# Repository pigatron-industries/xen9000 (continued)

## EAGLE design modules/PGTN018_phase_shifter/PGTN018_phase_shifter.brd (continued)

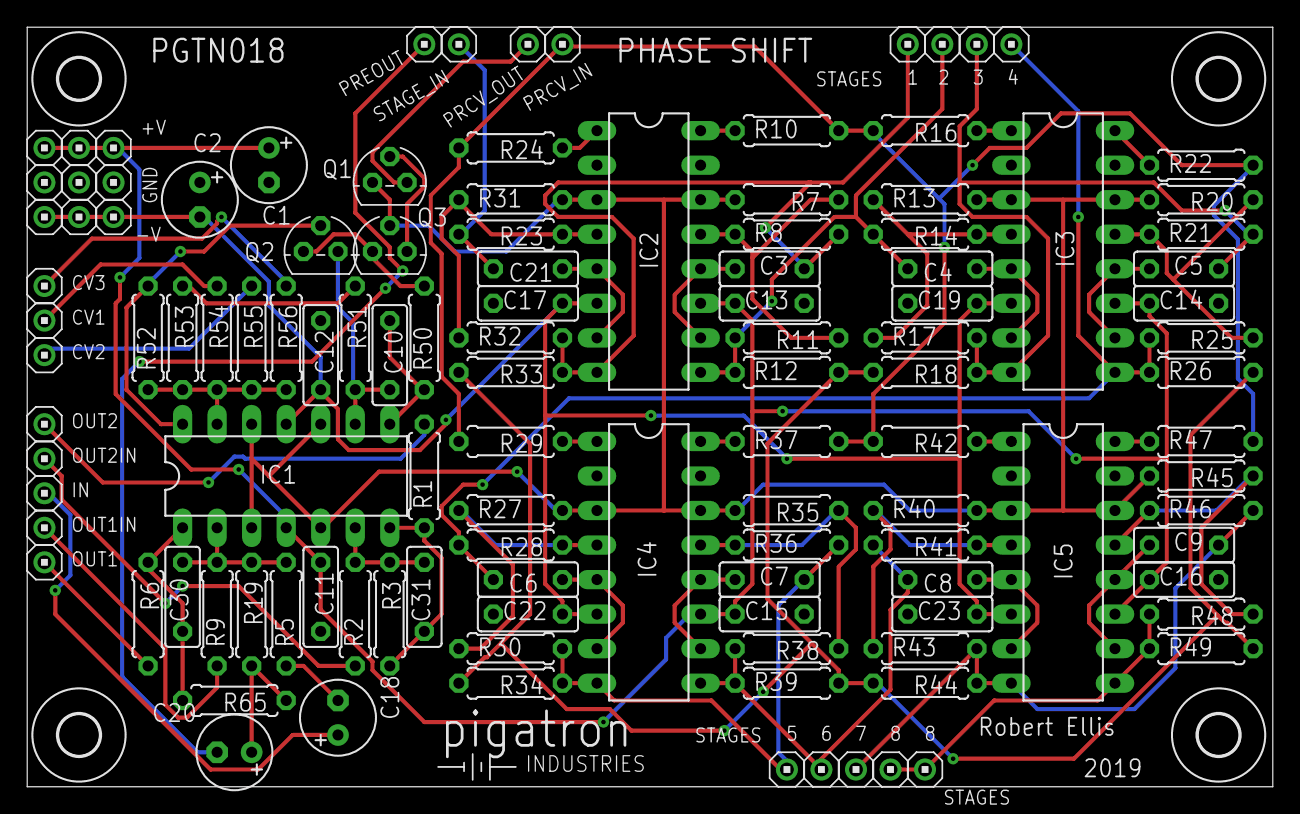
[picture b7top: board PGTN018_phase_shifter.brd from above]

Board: 2 copper layers, 91.6 x 55.9 mm, 123 parts (0 on the bottom side), 62 nets.

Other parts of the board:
U$1, U$2, U$3, U$4: STANDOFF/3.0
U$5: PIGATRON-LOGO

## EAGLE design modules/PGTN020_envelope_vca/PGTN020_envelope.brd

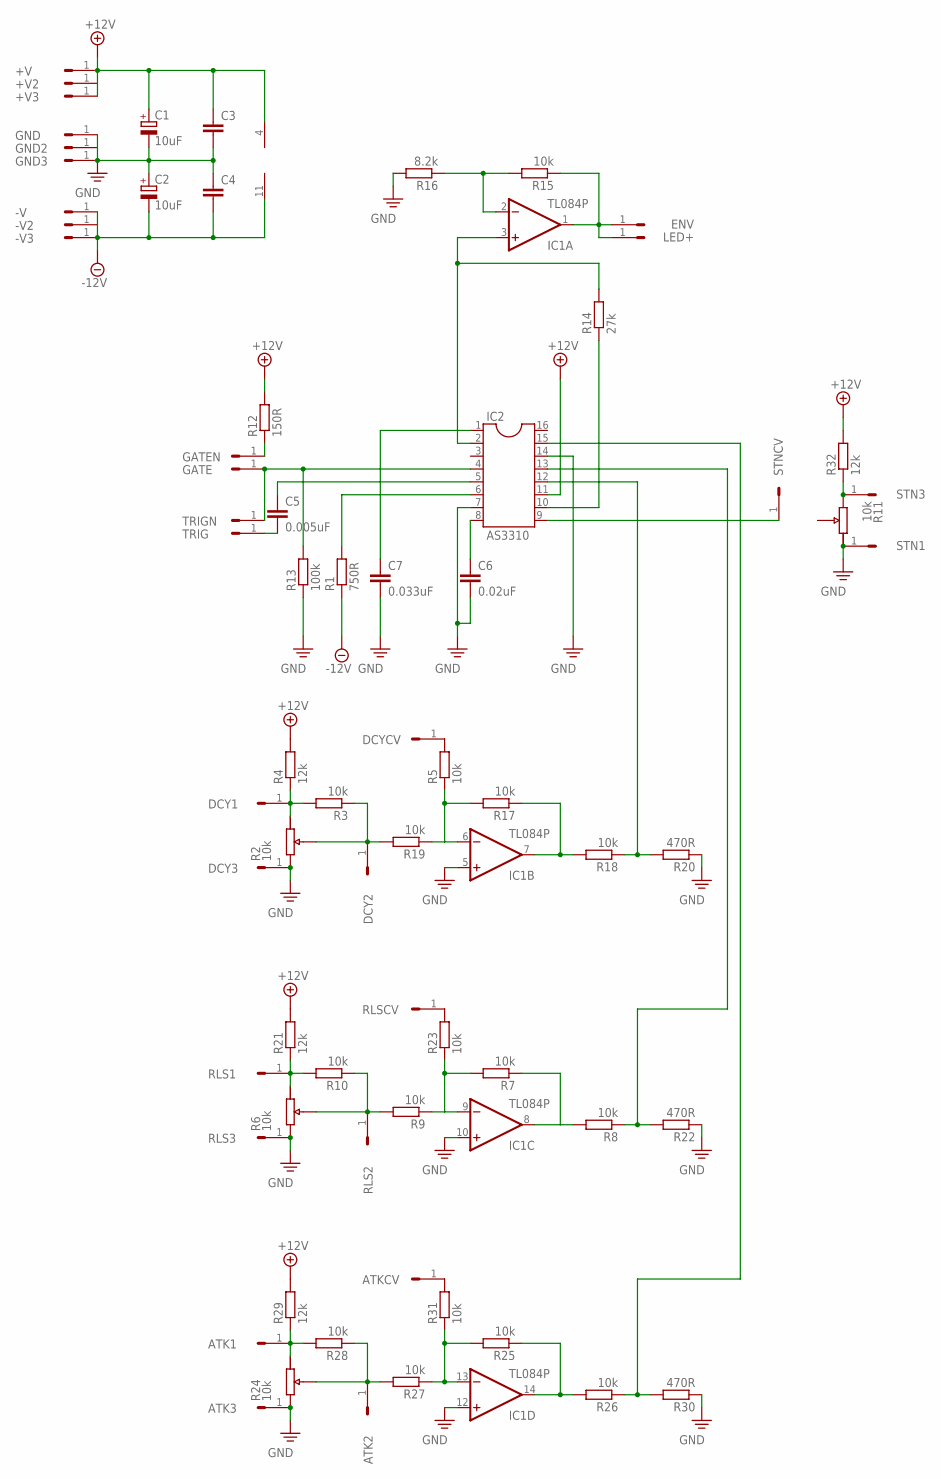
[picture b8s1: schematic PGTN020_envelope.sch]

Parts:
+V, +V2, +V3: HEADER/MALE/01
-V, -V2, -V3: HEADER/MALE/01
ATK1, ATK2, ATK3: HEADER/MALE/01
ATKCV: HEADER/MALE/01
C1, C2: 10uF; E2,5-6
C3, C4: CAPACITORCERAMICDISC/5; CERAMICDISC/5
C5: 0.005uF; CERAMICDISC/5
C6: 0.02uF; CERAMICDISC/5
C7: 0.033uF; CERAMICDISC/5
DCY1, DCY2, DCY3: HEADER/MALE/01
DCYCV: HEADER/MALE/01
ENV: HEADER/MALE/01
GATE: HEADER/MALE/01
GATEN: HEADER/MALE/01
GND, GND2, GND3: HEADER/MALE/01
IC1: TL084P; DIL14
IC2: AS3310; DIL16
LED+: HEADER/MALE/01
R1: 750R; RESISTOR/7.5
R3, R5, R7, R8, R9, R10, R15, R17, R18, R19, R23, R25, R26, R27, R28, R31: 10k; RESISTOR/7.5
R4, R21, R29, R32: 12k; RESISTOR/7.5
R12: 150R; RESISTOR/7.5
R13: 100k; RESISTOR/7.5
R14: 27k; RESISTOR/7.5
R16: 8.2k; RESISTOR/7.5
R20, R22, R30: 470R; RESISTOR/7.5
RLS1, RLS2, RLS3: HEADER/MALE/01
RLSCV: HEADER/MALE/01
STN1, STN3: HEADER/MALE/01
STNCV: HEADER/MALE/01
TRIG: HEADER/MALE/01
TRIGN: HEADER/MALE/01

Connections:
+12V: +V.1, +V2.1, +V3.1, C1.+, C3.1, IC1.4 (V+), IC2.11, R4.2, R12.2, R21.2, R29.2, R32.2
-12V: -V.1, -V2.1, -V3.1, C2.-, C4.2, IC1.11 (V-), R1.1
GND: ATK3.1, C1.-, C2.+, C3.2, C4.1, C6.2, DCY3.1, GND.1, GND2.1, GND3.1, IC1.5 (+IN), IC1.10 (+IN), IC1.12 (+IN), IC2.7, IC2.14, R13.1, R16.2, R20.1, R22.1, R30.1, RLS3.1, STN1.1
unnamed: IC2.9, STNCV.1
unnamed: GATEN.1, R12.1
unnamed: C5.1, IC2.5
unnamed: GATE.1, IC2.4, R13.2, TRIGN.1
unnamed: DCYCV.1, R5.2
unnamed: IC1.8 (OUT), R7.1, R8.2
unnamed: IC1.9 (-IN), R7.2, R9.1, R23.1
unnamed: R9.2, R10.1, RLS2.1
unnamed: C5.2, TRIG.1
unnamed: R10.2, R21.1, RLS1.1
unnamed: IC2.13, R8.1, R22.2
unnamed: IC2.6, R1.2
unnamed: C6.1, IC2.8
unnamed: C7.1, IC2.1
unnamed: IC1.2 (-IN), R15.2, R16.1
unnamed: IC2.10, R14.1
unnamed: IC1.3 (+IN), IC2.2, R14.2
unnamed: ENV.1, IC1.1 (OUT), LED+.1, R15.1
unnamed: IC1.7 (OUT), R17.1, R18.2
unnamed: IC1.6 (-IN), R5.1, R17.2, R19.1
unnamed: DCY2.1, R3.1, R19.2
unnamed: IC2.12, R18.1, R20.2
unnamed: DCY1.1, R3.2, R4.1
unnamed: R23.2, RLSCV.1
unnamed: IC1.14 (OUT), R25.1, R26.2
unnamed: IC1.13 (-IN), R25.2, R27.1, R31.1
unnamed: ATK2.1, R27.2, R28.1
unnamed: ATK1.1, R28.2, R29.1
unnamed: IC2.15, R26.1, R30.2
unnamed: ATKCV.1, R31.2
unnamed: R32.1, STN3.1
PE: C7.2

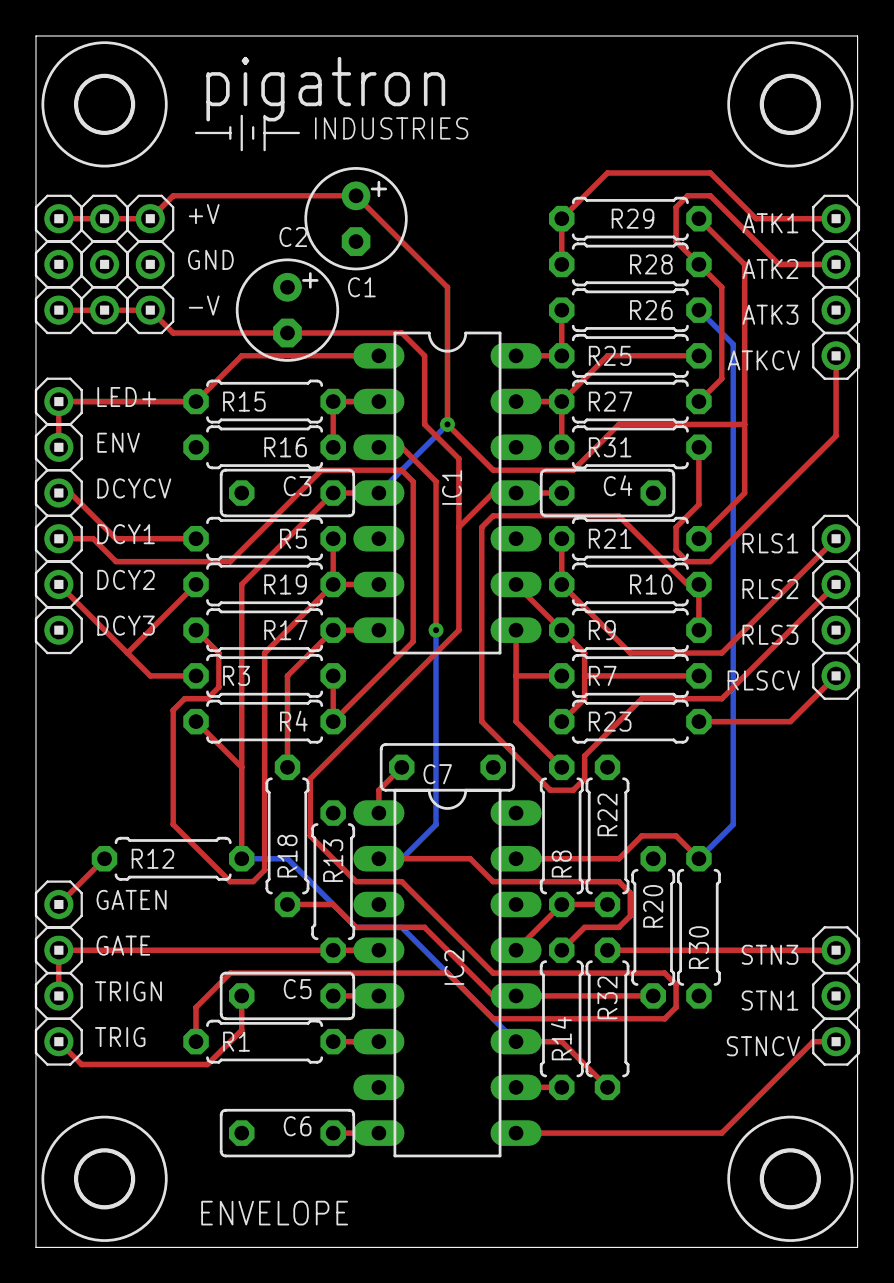
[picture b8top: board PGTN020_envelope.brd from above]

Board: 2 copper layers, 45.6 x 67.3 mm, 72 parts (0 on the bottom side), 34 nets.

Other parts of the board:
U$1, U$2, U$3, U$4: STANDOFF/3.0
U$5: PIGATRON-LOGO
